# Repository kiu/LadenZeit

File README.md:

# LadenZeit
LadenZeit - Never miss opening hours again. Minimalist OLED store tracker with rotary control

## Device

- [main](hardware/REV_B/main/): The main PCB
- [plate](hardware/REV_B/plate/): PCB used as backplate
- [mech](hardware/REV_B/mech/): OpenSCAD case
- [BOM](hardware/REV_B/LadenZeit-bom.pdf): Bill of materials

### Firmware (Arduino IDE)

- [source](firmware/LadenZeit/)
- [UI flow](firmware/ladenzeit-ui-flow.drawio.png)

Arduino IDE config
- Board: [ESP32C3 Dev Module](https://github.com/espressif/arduino-esp32)
- Library: [U8g2](https://github.com/olikraus/u8g2)
- Library: [ESP32Time](https://github.com/fbiego/ESP32Time)
- Config: "USB CDC On Boot: Enabled"
- Config: "CPU Frequency: 80MHz (WiFi)"
- Config: "Partition Scheme: Huge APP (3MB No OTA/1MB SPIFFFS)"

## Server (Java Spring Boot)

- [source](server/LadenZeitServer)
- [single file frontend](server/index.html)
- [service](server/ladenzeit.service)

Inject Google Maps API key via environment.

# License
This project is licensed under the Creative Commons Attribution-NonCommercial 3.0 Unported (CC BY-NC 3.0) license.

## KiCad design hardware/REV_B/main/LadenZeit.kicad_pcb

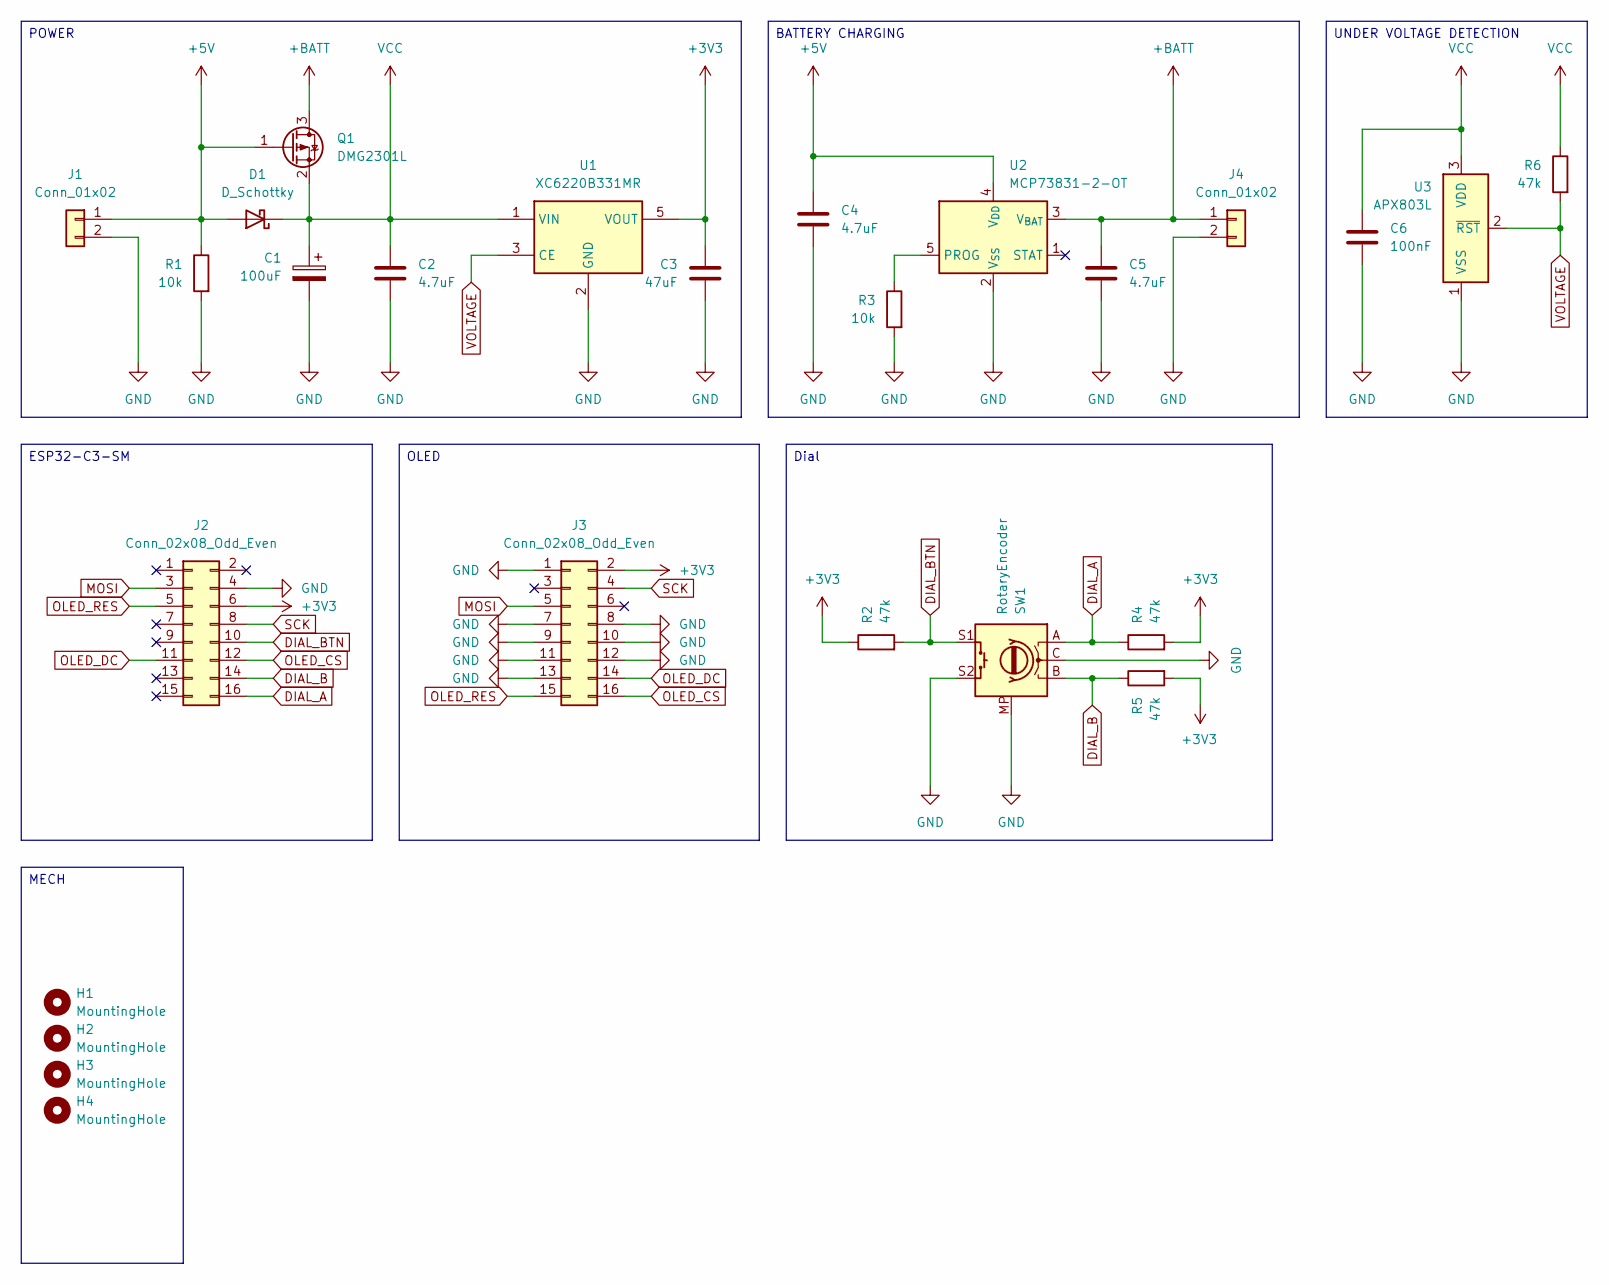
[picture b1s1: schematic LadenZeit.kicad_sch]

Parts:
C1: 100uF; CP_EIA-7343-43_Kemet-X_HandSolder; LCSC C554014
C2, C4, C5: 4.7uF; C_0805_2012Metric; LCSC C1779
C3: 47uF; C_0805_2012Metric; LCSC C19103846
C6: 100nF; C_0805_2012Metric; LCSC C49678
D1: D_Schottky; D_SOD-123; LCSC C8598
H1, H2, H3, H4: MountingHole; MountingHole_3.2mm_M3_DIN965
J1: Conn_01x02; USB MG0175M
J2: Conn_02x08_Odd_Even; ESP32-C3-SM-SMT
J3: Conn_02x08_Odd_Even; PinSocket_2x08_P2.54mm_Vertical
J4: Conn_01x02; JST_PH_S2B-PH-K_1x02_P2.00mm_Horizontal-Multi; LCSC C131337
Q1: DMG2301L; SOT-23; LCSC C102619
R1, R3: 10k; R_0805_2012Metric; LCSC C2930231
R2, R4, R5, R6: 47k; R_0805_2012Metric; LCSC C17713
SW1: RotaryEncoder; RotaryEncoder_Alps_EC11E-Switch_Vertical_H20mm; LCSC C143790
U1: XC6220B331MR; SOT-23-5; LCSC C86534
U2: MCP73831-2-OT; SOT-23-5; LCSC C424093
U3: APX803L; SOT-23; LCSC C2067862

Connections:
+3V3: C3.1, J2.6, J3.2, R2.1, R4.2, R5.2, U1.5 (VOUT)
+5V: C4.1, D1.2 (A), J1.1, Q1.1 (G), R1.1, U2.4 (V_{DD})
+BATT: C5.1, J4.1, Q1.3 (D), U2.3 (V_{BAT})
DIAL_A: J2.16, R4.1, SW1.A
DIAL_B: J2.14, R5.1, SW1.B
DIAL_BTN: J2.10, R2.2, SW1.S1
GND: C1.2, C2.2, C3.2, C4.2, C5.2, C6.2, J1.2, J2.4, J3.1, J3.7, J3.8, J3.9, J3.10, J3.11, J3.12, J3.13, J4.2, R1.2, R3.2, SW1.C, SW1.MP, SW1.S2, U1.2 (GND), U2.2 (V_{SS}), U3.1 (VSS)
MOSI: J2.3, J3.5
unnamed: R3.1, U2.5 (PROG)
OLED_CS: J2.12, J3.16
OLED_DC: J2.11, J3.14
OLED_RES: J2.5, J3.15
SCK: J2.8, J3.4
VCC: C1.1, C2.1, C6.1, D1.1 (K), Q1.2 (S), R6.1, U1.1 (VIN), U3.3 (VDD)
VOLTAGE: R6.2, U1.3 (CE), U3.2 (~RST)

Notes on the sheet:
UNDER VOLTAGE DETECTION
ESP32-C3-SM
POWER
BATTERY CHARGING
MECH
Dial
OLED

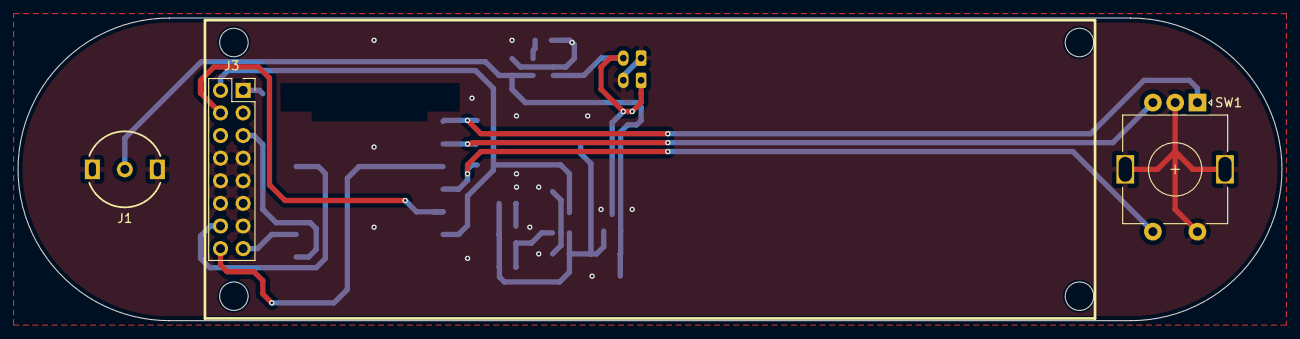
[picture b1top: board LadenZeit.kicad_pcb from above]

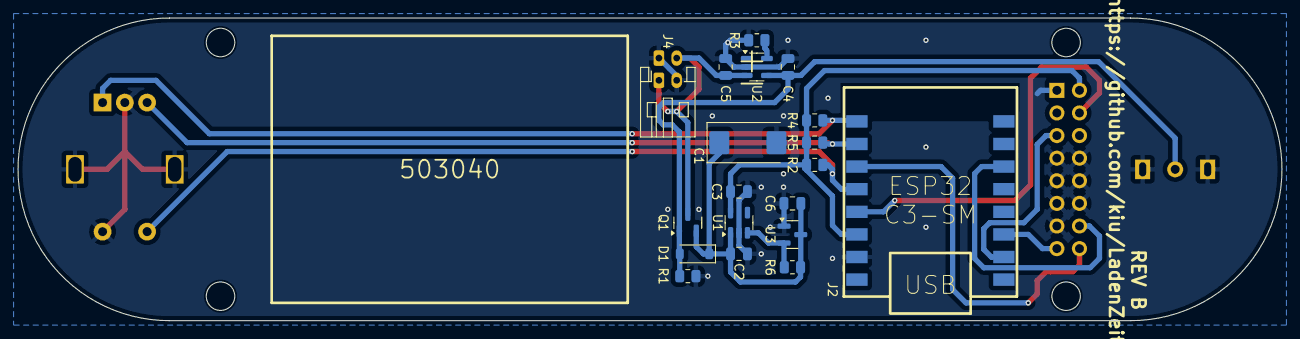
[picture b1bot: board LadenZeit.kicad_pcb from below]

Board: 2 copper layers, 142.0 x 34.0 mm, 26 parts (19 on the bottom side), 15 nets.

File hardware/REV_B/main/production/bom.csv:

Designator,Footprint,Quantity,Value,LCSC Part #
C1,CP_EIA-7343-43_Kemet-X_HandSolder,1,100uF,C554014
"C2, C4, C5",0805,3,4.7uF,C1779
C3,0805,1,47uF,C19103846
C6,0805,1,100nF,C49678
D1,D_SOD-123,1,D_Schottky,C8598
J1,USB MG0175M,1,Conn_01x02,
J2,ESP32-C3-SM-SMT,1,Conn_02x08_Odd_Even,
J3,PinSocket_2x08_P2.54mm_Vertical,1,Conn_02x08_Odd_Even,C30734
J4,JST_PH_S2B-PH-K_1x02_P2.00mm_Horizontal-Multi,1,Conn_01x02,C131337
Q1,SOT-23,1,DMG2301L,C102619
"R1, R3",0805,2,10k,C2930231
"R2, R4, R5, R6",0805,4,47k,C17713
SW1,RotaryEncoder_Alps_EC11E-Switch_Vertical_H20mm,1,RotaryEncoder,C143790
U1,SOT-23-5,1,XC6220B331MR,C86534
U2,SOT-23-5,1,MCP73831-2-OT,C424093
U3,SOT-23,1,APX803L,C2067862

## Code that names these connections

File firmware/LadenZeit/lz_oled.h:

#ifndef LZ_OLED_H
#define LZ_OLED_H

#include <Arduino.h>

#define PIN_OLED_CLK 4
#define PIN_OLED_MOSI 6
#define PIN_OLED_CS 2
#define PIN_OLED_DC 10
#define PIN_OLED_RES 7

// Selectable cells visible per screen — drives both nav paging (mainNavPerPage
// in the state handlers) and the matching render loops in lz_oled.cpp.
#define PLACES_PER_PAGE 4
#define MENU_PER_PAGE 4
#define WIFI_SSID_PER_PAGE 2
#define WIFI_PASS_PER_PAGE 16
#define DETAIL_DAYS_PER_PAGE 2

void oledSetup();
void oledBufferClear();
void oledBufferSend();
void oledEnabled(bool enabled);
uint8_t oledFlipGet();
void oledFlipSet(bool flip);

void oledShowSplash();

void oledShowWifiSsid(uint8_t navStart, uint8_t selected);
void oledShowWifiSsidManual(const char* ssid, uint8_t navStart, uint8_t selected);
void oledShowWifiPass(const char* ssid, const char* pass, uint8_t navStart, uint8_t selected);

void oledShowPlacesList(uint8_t navStart, uint8_t entries, uint8_t selected);
void oledShowPlacesListError(const char* text1, const char* text2, uint8_t selected);
void oledShowPlacesDetail(uint8_t pidx, uint8_t navStart, uint8_t selected);

void oledShowMenu(uint8_t navStart, uint8_t selected);

void oledShowDialog(const char* head, const char* msg, uint8_t btnCount, const char* btns[], uint8_t selected);

void oledShowConnectionStatus(uint8_t wifi, uint8_t data);

#endif
